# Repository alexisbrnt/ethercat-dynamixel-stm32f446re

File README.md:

# EtherCAT Communication for Dynamixel by STM32F446RE

> An embedded **EtherCAT slave node** built around the STM32F446RE, driving a Dynamixel XM430-W350 servomotor in real time.

---

## About

An embedded EtherCAT slave node based on the **STM32F446RE** microcontroller, designed to drive a **Dynamixel XM430-W350** servomotor through the Dynamixel Protocol 2.0. The STM32 interfaces with an EtherCAT master over SPI (via a LAN9252 slave controller) and translates incoming commands into UART/RS-485 frames sent to the motor.

This project is developed as part of an internship at **Heemskerk Innovative Technology (HIT)**, Delft, The Netherlands.

---

## Goal

Design and implement a new real-time communication architecture allowing an EtherCAT master to command a Dynamixel servomotor (position, velocity, etc.) and read back its live telemetry (position, velocity, current, temperature) with deterministic timing.

**Data path:**

```
EtherCAT Master  ──►  LAN9252 (SPI slave)  ──►  STM32F446RE  ──►  MAX485  ──►  Dynamixel XM430-W350
```

---

## Hardware

| Component | Reference |
|---|---|
| Microcontroller | STM32F446RE (ARM Cortex-M4 @ 180 MHz, 512 KB Flash, 128 KB SRAM) |
| Development board | Nucleo-F446RE (integrated ST-LINK) |
| EtherCAT slave controller | **EVB-LAN9252-SPI** (Microchip evaluation board) |
| Motor | Dynamixel XM430-W350 (Protocol 2.0) |
| UART ↔ RS-485 transceiver | MAX485 |
| Motor power supply | SMPS2Dynamixel |

---

## STM32F446RE Pinout

### Dynamixel communication (UART + RS-485)

| STM32 Pin | Function | Connected to |
|---|---|---|
| **PA9** | UART TX | MAX485 DI |
| **PA10** | UART RX | MAX485 RO |
| **PB3** | DE/RE (RS-485 direction control) | MAX485 DE + RE |

### EtherCAT communication (SPI to LAN9252)

| STM32 Pin | Function | Connected to |
|---|---|---|
| **PA5** | SPI SCK | LAN9252 SCK |
| **PA6** | SPI MISO | LAN9252 MISO |
| **PA7** | SPI MOSI | LAN9252 MOSI |
| **PB6** | SPI CS | LAN9252 CS |

---

## Configuration

| Parameter | Value |
|---|---|
| UART baudrate (STM32 ↔ Dynamixel) | **3,000,000 bauds** (3 Mbps) |
| Dynamixel protocol | **2.0** |
| Default motor ID | **1** |
| SPI frequency (STM32 ↔ LAN9252) | **11.25 MHz** |
| EtherCAT cycle time | **2 ms** |

---

## Usage

### 1. Flash the LAN9252 EEPROM (one-time setup)

Before the EtherCAT master can discover the slave with the correct identity (vendor ID, product code, PDO mapping, etc.), the LAN9252 EEPROM must be programmed with the project's ESI (EtherCAT Slave Information) binary.

The EEPROM image is provided in the firmware sources:

```
STM32_dynamixel/Src/ECAT/soes-esi/eeprom.hex
```

Flash it with the `eepromtool` utility provided by [SOEM](https://github.com/OpenEtherCATsociety/SOEM):

```bash
sudo ./eepromtool <your_network_interface> 1 -wi eeprom.hex
```

- The first argument `1` is the EtherCAT slave position on the bus.
- Replace `<your_network_interface>` (e.g. `eth0`) with the interface connected to the LAN9252.

This step is only required **once per LAN9252 board**, or whenever the ESI / PDO mapping is changed.

### 2. Build and flash the STM32 firmware

1. Open **STM32CubeIDE** 
2. `File → Open Projects from File System…` and select the `firmware/` folder.
3. Build the project: `Project → Build Project` (or `Ctrl+B`).
4. Connect the Nucleo-F446RE over USB and flash: `Run → Run` (or `F11` for debug mode).

### 3. Run the EtherCAT master and GUI

The `ec_motor.py` script is a single-program tool that launches the **EtherCAT master** (using `pysoem`) and a **PyQt5 graphical interface** in the same process. The master runs its cyclic loop (2 ms period) in a dedicated thread and communicates with the GUI through Qt signals.

The GUI allows the user to:

- select the motor **ID** and **control mode** (Position or Velocity),
- set a **target position** (0–4095) or **target velocity** (−200 to +200) through sliders,
- toggle the **torque** and the **LED** on the motor,
- monitor in real time the **present position, velocity, current, temperature**, the motor **state** (`IDLE`, `INIT`, `READY`, `RUNNING`, `ERROR`, `OFF`), the current **operating mode** and the **baudrate**.

**Dependencies** (tested on Linux, Ubuntu/Debian):

```bash
pip install -r scripts/requirements.txt
```

**Launch** (from the root of the repository):

```bash
sudo python3 scripts/ec_motor.py --ifname <your_network_interface>
```

#### Network interface — must be adapted to your machine

The EtherCAT master binds to a specific network interface (the one physically connected to the EtherCAT slave, typically a USB-to-Ethernet adapter). The interface name depends on your hardware and operating system, so **it must be changed in two places**:

1. In the **launch command**, via the `--ifname` argument.
2. In the **default value** inside `scripts/ec_motor.py` (the current hardcoded default is the interface used during development and will not match your setup).

To find the name of your own interface on Linux:

```bash
ip link show
```

Look for an entry matching the adapter you plugged in (often starting with `enx...` for USB-to-Ethernet, or `eth...` / `enp...` for built-in Ethernet).

**Other notes:**

- `sudo` is required because the EtherCAT master sends raw Ethernet frames directly on the network interface.

---

## Resources & references

- [Dynamixel XM430-W350 e-Manual](https://emanual.robotis.com/docs/en/dxl/x/xm430-w350/)
- [Dynamixel Protocol 2.0](https://emanual.robotis.com/docs/en/dxl/protocol2/)
- [STM32F446RE datasheet](https://www.st.com/en/microcontrollers-microprocessors/stm32f446re.html)
- [Microchip LAN9252 product page](https://www.microchip.com/en-us/product/lan9252)
- [EtherCAT Technology Group (ETG)](https://www.ethercat.org/)

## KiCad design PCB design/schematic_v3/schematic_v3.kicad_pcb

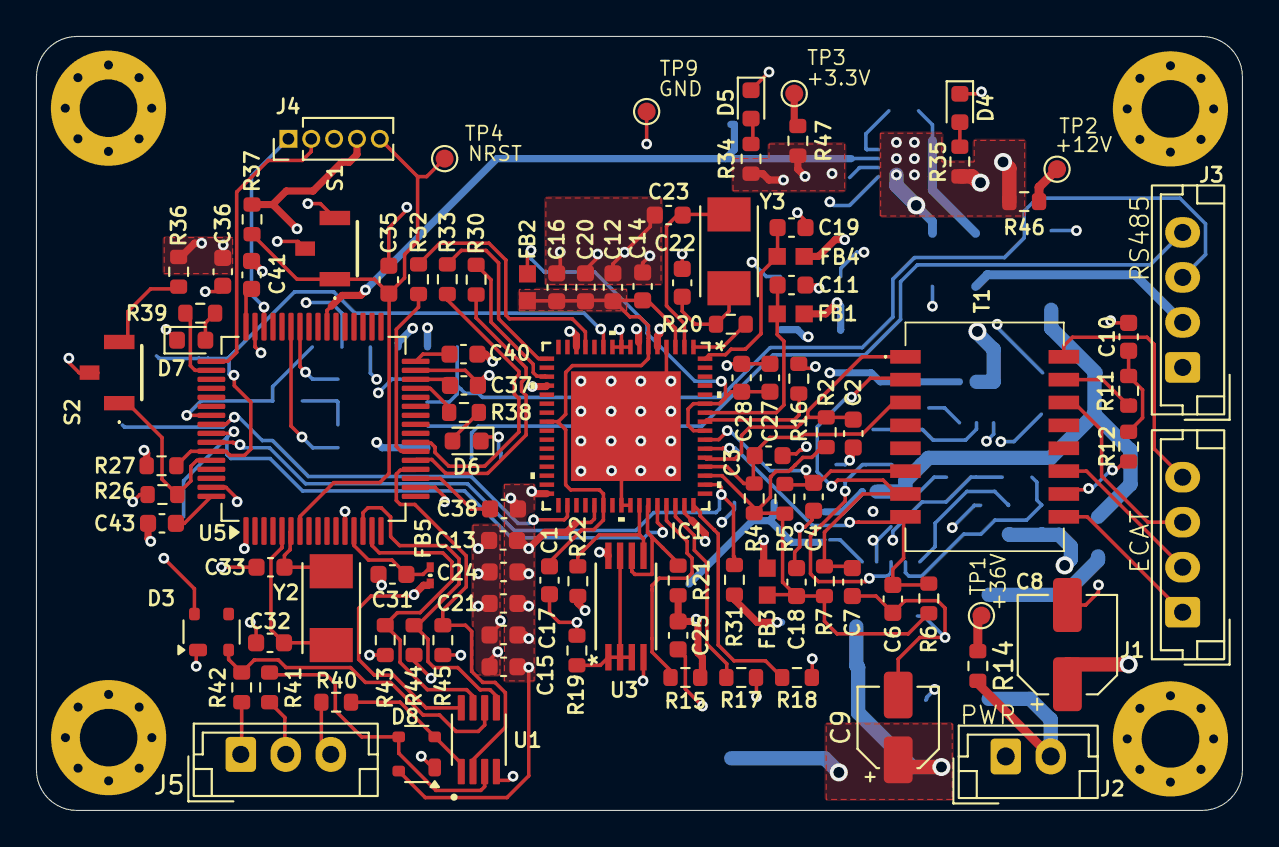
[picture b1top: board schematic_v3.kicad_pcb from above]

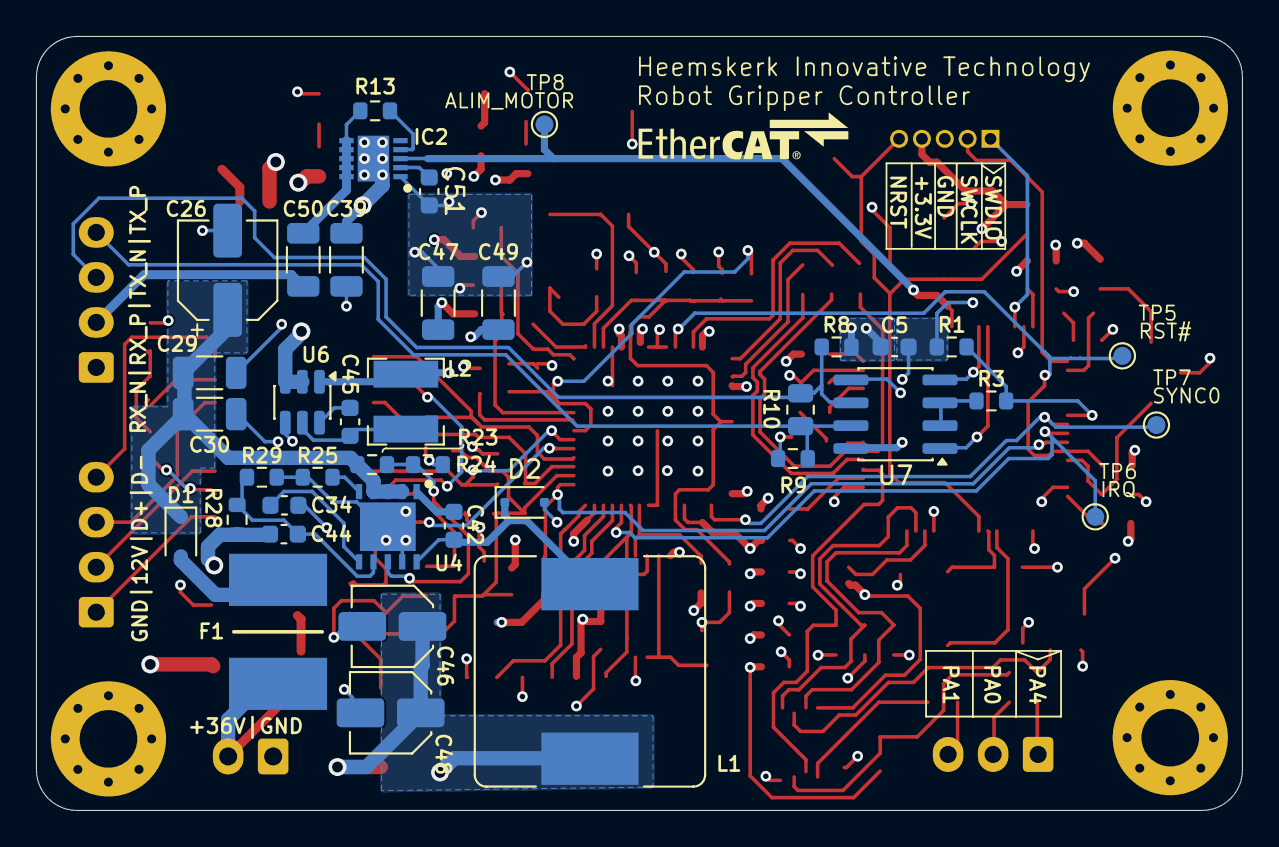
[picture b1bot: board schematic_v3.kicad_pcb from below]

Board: 4 copper layers, 67.0 x 43.0 mm, 145 parts (39 on the bottom side), 93 nets.

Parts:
C1, C5, C11, C13, C15, C16, C17, C20, C21, C24, C25, C27, C28, C31, C34, C35, C38, C40, C41, C42, C43, C45: 100n; C_0603_1608Metric
C2, C3, C4, C6: 10p; C_0603_1608Metric
C7: 0.022u; C_0603_1608Metric
C8: 10u; CP_Elec_5x5.4
C9: 1u; CP_Elec_4x5.4
C10: 1n; C_0603_1608Metric
C12, C18, C19, C36: 1u; C_0603_1608Metric
C14: 470p; C_0603_1608Metric
C22, C23: 18p; C_0603_1608Metric
C26: 47u; CP_Elec_5x5.4
C29, C39, C50: 10u; C_1206_3216Metric
C30: 100n; C_1206_3216Metric
C32, C33: 27p; C_0603_1608Metric
C37: 4.7u; C_0603_1608Metric
C44: 270p; C_0603_1608Metric
C46, C48: 27u; C_Elec_4x5.8
C47, C49: 22u; C_1206_3216Metric
C51: 56p; C_0603_1608Metric
D1, D2: PMEG3020EJ; D_SOD-323F
D3, D8: PRTR5V0U2X; SOT-143
D4, D5, D6, D7: LED_Small; LED_0603_1608Metric
F1: 2920L150_60MR
FB1, FB2, FB3, FB4: BLM18EG221SN1D; IND_BLM18_0603_MUR
FB5: MMZ0603A471ET000
H1, H2, H3, H4: MountingHole; MountingHole_3.2mm_M3_Pad_Via
IC1: LAN9252
IC2: SON50P300X300X100-11N-D; MP5000ADQ-LF-Z
J1: Conn_01x04_Pin; JST_EH_B4B-EH-A_1x04_P2.50mm_Vertical
J2: Conn_01x02_Pin; JST_EH_B2B-EH-A_1x02_P2.50mm_Vertical
J3: connection_moteur; JST_EH_B4B-EH-A_1x04_P2.50mm_Vertical
J4: Conn_01x05_Pin; PinHeader_1x05_P1.27mm_Vertical
J5: Conn_01x03_Pin; JST_EH_B3B-EH-A_1x03_P2.50mm_Vertical
L1: 18u; L_Bourns_SRR1260
L2: 6.8u; L_Bourns-SRN4018
R1: 47k; R_0603_1608Metric
R2, R4, R5, R6: 49.9; R_0603_1608Metric
R3, R15, R17, R18, R24, R26, R27, R29, R31, R37, R43, R44, R45: 10k; R_0603_1608Metric
R7, R20: 0; R_0603_1608Metric
R8, R9, R25: 20k; R_0603_1608Metric
R10: 120; R_0805_2012Metric
R11, R12: 75; R_0603_1608Metric
R13: 220; R_0603_1608Metric
R14, R46, R47: 100; R_0603_1608Metric
R16: 12.1k; R_0603_1608Metric
R19: 4.7k; R_0603_1608Metric
R21, R22, R34, R36, R38, R39, R40, R41, R42: 1k; R_0603_1608Metric
R23: 68k; R_0603_1608Metric
R28: 150k; R_0603_1608Metric
R30, R32, R33: 33; R_0603_1608Metric
R35: 3.3k; R_0603_1608Metric
S1, S2: B3U-1100PM; B3U1100PM
T1: 7490100110A
TP1, TP2, TP3, TP4, TP5, TP6, TP7, TP8, TP9: TestPoint; TestPoint_Pad_D1.0mm
U1: SN74LVC3G17DCTRE4
U3: 24FC512-I/ST; 24FC512_I_ST
U4: LMR14030SQDPRTQ1
U5: STM32F446RETx; LQFP-64_10x10mm_P0.5mm
U6: AP63203WU; TSOT-23-6
U7: MAX3485; SOIC-8_3.9x4.9mm_P1.27mm
Y2: ABM3-20.000MHZ-D2Y-T
Y3: ABM3-25.000MHZ-D2Y-T

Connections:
+3.3V: C5.1, C13.1, C15.1, C17.1, C21.1, C24.1, C25.2, C36.2, C38.1, C40.1, C41.1, C43.1, C47.1, C49.1, D3.4 (VCC), D8.4 (VCC), FB1.1, FB3.2, FB4.2, FB5.1, IC1.5 (VDD33), IC1.7 (REG_EN), IC1.14 (VDDIO0), IC1.20 (VDDIO1), IC1.32 (VDDIO2), IC1.37 (VDDIO3), IC1.47 (VDDIO4), J4.4, L2.2, R8.2, R15.1, R21.2, R22.2, R27.1, R31.1, R34.1, R36.1, R37.2, R47.2, U1.8 (VCC), U3.8 (VCC), U5.1 (VBAT), U6.1 (FB), U7.8 (VCC)
+12V: C8.1, C9.1, C39.1, C44.1, C46.1, C48.1, IC2.11 (VCC), L1.2, R28.1, R35.1, R46.2, U6.2 (EN), U6.3 (IN)
+36V: F1.1, J2.2, R14.2
/ALIM_MOTOR: IC2.3 (ENABLE/FAULT), TP8.1 (1_1), U5.39 (PC8)
/AVDD: C31.1, FB5.2, U5.13 (VDDA)
/AX: R19.1, U3.1 (A0), U3.2 (A1), U3.3 (A2), U3.7 (WP)
/BOOT: C42.1, U4.1 (BOOT)
/BOOT0: R26.1, S2.1 (COM), U5.60 (BOOT0)
/BST: C45.2, U6.6 (BST)
/CMT: C10.1, R11.1, R12.1
/CMT1: R11.2, T1.15 (CTX)
/CMT2: R12.2, T1.10 (CRX)
/DATA+: J3.3, R8.1, R10.2, U7.6 (A)
/DATA-: J3.4, R9.2, R10.1, U7.7 (B)
/DE/RE: R3.1, U7.2 (~RE), U7.3 (DE)
/DI: U5.42 (PA9), U7.4 (DI)
/FB: C44.2, R28.2, R29.1, U4.7 (FB)
/I2C_SCL: IC1.43 (EESCL/TCK), R21.1, U3.6 (SCL)
/I2C_SDL: IC1.42 (EESDA/TMS), R22.1, U3.5 (SDA)
/IRQ: IC1.44 (IRQ), TP6.1 (1_1), U5.57 (PB5)
/MISO: IC1.13 (D1/AD1/EOF/SO/SIO1), R32.1
/MOSI: IC1.17 (D0/AD0/WD_STATE/SI/SIO0), R33.1
/NRST: C35.2, J4.5, R37.1, S1.1 (COM), TP4.1 (1_1), U5.7 (NRST)
/OSCI: IC1.1 (OSCI), R20.1
/OSCO: C23.2, IC1.2 (OSCO), Y3.1
/PA0: R44.1, U1.5 (2Y), U5.14 (PA0)
/PA1: R43.1, U1.7 (1Y), U5.15 (PA1)
/PA4: R45.1, U1.2 (3Y), U5.20 (PA4)
/PA5: R30.2, U5.21 (PA5)
/PA6: R32.2, U5.22 (PA6)
/PA7: R33.2, U5.23 (PA7)
/PA15: R39.1, U5.50 (PA15)
/PB10: R38.1, U5.29 (PB10)
/PGOOD: R23.2, R24.1, U4.8 (PGOOD)
/PH0: C32.2, U5.5 (PH0), Y2.2
/PH1: C33.2, U5.6 (PH1), Y2.1
/RBIAS: IC1.57 (RBIAS), R16.2
/RCT: C7.1, R7.2, T1.2 (CTD), T1.7 (CRD)
/RO: U5.43 (PA10), U7.1 (RO)
/RS485_MODE: R1.2, R3.2, U5.55 (PB3)
/RST#: IC1.11 (RST#), R27.2, TP5.1 (1_1), U5.59 (PB7)
/RT_SYNC: R25.1, U4.5 (RT_SYNC)
/RXA_N: C6.1, IC1.54 (RXNA), R6.2, T1.8 (RD-)
/RXA_P: C4.1, IC1.55 (RXPA), R5.2, T1.6 (RD+)
/RX_N: J1.1, T1.9 (RX-)
/RX_P: J1.2, T1.11 (RX+)
/SCK: IC1.19 (D9/AD9/LATCH_IN/SCK), R30.1
/SCS#: IC1.50 (D5/AD5/OUTVALID/SCS#), R31.2, U5.58 (PB6)
/SS: C34.1, U4.6 (SS)
/SW: C45.1, L2.1, U6.5 (SW)
/SWCLK: J4.2, U5.49 (PA14)
/SWDIO: J4.1, U5.46 (PA13)
/SYNC0: IC1.34 (SYNC0/LATCH0), TP7.1 (1_1), U5.56 (PB4)
/TXA_N: C3.1, IC1.52 (TXNA), R4.2, T1.3 (TD-)
/TXA_P: C2.1, IC1.53 (TXPA), R2.2, T1.1 (TD+)
/TX_N: J1.3, T1.14 (TX-)
/TX_P: J1.4, T1.16 (TX+)
/VCAP_1: C37.1, U5.30 (VCAP_1)
/VDD12TX1: C27.1, C28.1, FB2.2, IC1.56 (VDD12TX1), IC1.59 (VDD12TX2)
/VDD19: C38.2, U5.19 (VDD)
/VDD32: C40.2, U5.32 (VDD)
/VDD33BIAS: C11.2, FB1.2, IC1.58 (VDD33BIAS)
/VDD33TXRX1: C18.1, FB3.1, IC1.51 (VDD33TXRX1), R2.1, R4.1, R5.1, R6.1, R7.1
/VDD33TXRX2: C19.1, FB4.1, IC1.64 (VDD33TXRX2)
/VDD48: C41.2, U5.48 (VDD)
/VDD64: C43.2, U5.64 (VDD)
/VDDCR: C1.2, C12.1, C14.1, C16.1, C20.1, FB2.1, IC1.3 (OSCVDD12), IC1.6 (VDDCR0), IC1.24 (VDDCR1), IC1.38 (VDDCR2)
/VIN: C26.1, C29.1, C30.1, D1.1 (K), R23.1, U4.2 (VIN), U4.3 (VIN), U4.4 (EN)
GND: C1.1, C2.2, C3.2, C4.2, C5.2, C6.2, C7.2, C8.2, C9.2, C11.1, C12.2, C13.2, C14.2, C15.2, C16.2, C17.2, C18.2, C19.2, C20.2, C21.2, C22.1, C23.1, C24.2, C25.1, C26.2, C27.2, C28.2, C29.2, C30.2, C31.2, C32.1, C33.1, C34.2, C35.1, C36.1, C37.2, C39.2, C46.2, C47.2, C48.2, C49.2, C51.1, D2.2 (A), D3.1 (GND), D4.1 (K), D5.1 (K), D6.1 (K), D7.1 (K), D8.1 (GND), IC1.4 (OSCVSS), IC1.8 (FXLOSEN), IC1.9 (FXSDA/FXLOSA/FXSDENA), IC1.10 (FXSDB/FXLOSB/FXSDENB), IC1.40 (D8/AD8/DIGIO2/GPI2/GPO2/MII_MDIO), IC1.41 (TESTMODE), IC1.65 (VSS), IC2.1 (GND), J2.1, J3.1, J4.3, R1.1, R9.1, R16.1, R17.1, R18.1, R19.2, R24.2, R25.2, R26.2, R29.2, R43.2, R44.2, R45.2, S1.2 (NO), S1.3 (GND), S2.3 (GND), TP9.1 (1_1), U1.4 (GND), U3.4 (VSS), U4.9 (GND), U4.11 (PAD), U5.12 (VSSA), U5.18 (VSS), U5.31 (VSS), U5.47 (VSS), U5.63 (VSS), U6.4 (GND), U7.5 (GND)
unnamed: C22.2, R20.2, Y3.2
unnamed: D1.2 (A), F1.2
unnamed: C42.2, D2.1 (K), L1.1, U4.10 (SW)
unnamed: D3.2 (I/O1), R42.1, U1.6 (3A)
unnamed: D4.2 (A), R35.2
unnamed: D5.2 (A), R34.2
unnamed: D6.2 (A), R38.2
unnamed: D7.2 (A), R39.2
unnamed: D8.2 (I/O1), R40.1, U1.1 (1A)
unnamed: D8.3 (I/O2), R41.1, U1.3 (2A)
unnamed: IC1.48 (LINKACTLED0/TDO/CHIP_MODE0), R18.2
unnamed: IC1.46 (LINKACTLED1/TDI/CHIP_MODE1), R17.2
unnamed: IC1.45 (RUNLED/E2PSIZE), R15.2
unnamed: C51.2, IC2.2 (DV/DT)
unnamed: IC2.4 (I-LIMIT), R13.1
unnamed: C50.1, IC2.6 (SOURCE_1), IC2.7 (SOURCE_2), IC2.8 (SOURCE_3), IC2.9 (SOURCE_4), IC2.10 (SOURCE_5), R13.2
unnamed: C50.2, J3.2
unnamed: J5.1, R42.2
unnamed: J5.2, R41.2
unnamed: J5.3, R40.2
unnamed: R14.1, TP1.1 (1_1)
unnamed: R46.1, TP2.1 (1_1)
unnamed: R47.1, TP3.1 (1_1)
unnamed: R36.2, S2.2 (NO)

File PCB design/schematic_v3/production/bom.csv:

Designator,Footprint,Quantity,Value,LCSC Part #
"C1, C11, C13, C15, C16, C17, C20, C21, C24, C25, C27, C28, C31, C34, C35, C38, C40, C41, C42, C43, C45, C5",603,22,100n,C1525
C10,603,1,1n,C1588
"C12, C18, C19, C36",603,4,1u,C15849
C14,603,1,470p,C1620
"C2, C3, C4, C6",603,4,10p,C1634
"C22, C23",603,2,18p,C1647
C26,CP_Elec_5x5.4,1,47u,C7469972
"C29, C39, C50",1206,3,10u,C13585
C30,1206,1,100n,C24497
"C32, C33",603,2,27p,C107045
C37,603,1,4.7u,C19666
C44,603,1,270p,C1608
"C46, C48",C_Elec_4x5.8,2,27u,C413624
"C47, C49",1206,2,22u,C12891
C51,603,1,56p,C107053
C7,603,1,0.022u,C21122
C8,CP_Elec_5x5.4,1,10u,C7469956
C9,CP_Elec_4x5.4,1,1u,C3348
"D1, D2",D_SOD-323F,2,PMEG3020EJ,C7472895
"D3, D8",SOT-143,2,PRTR5V0U2X,C2827688
D4,603,1,LED_Small,C2286
D5,603,1,LED_Small,C2287
D6,603,1,LED_Small,C2288
D7,603,1,LED_Small,C2289
F1,2920L150_60MR,1,2920L150_60MR,C22504886
"FB1, FB2, FB3, FB4",IND_BLM18_0603_MUR,4,BLM18EG221SN1D,C85827
FB5,MMZ0603A471ET000,1,MMZ0603A471ET000,C502003
IC1,LAN9252,1,LAN9252,C2758355
IC2,MP5000ADQ-LF-Z,1,MP5000ADQ-LF-Z,C17698177
J1,JST_EH_B4B-EH-A_1x04_P2.50mm_Vertical,1,Conn_01x04_Pin,C160258
J2,JST_EH_B2B-EH-A_1x02_P2.50mm_Vertical,1,Conn_01x02_Pin,C160262
J3,JST_EH_B4B-EH-A_1x04_P2.50mm_Vertical,1,connection_moteur,C160258
J4,PinHeader_1x05_P1.27mm_Vertical,1,Conn_01x05_Pin,C22438102
J5,JST_EH_B3B-EH-A_1x03_P2.50mm_Vertical,1,Conn_01x03_Pin,C160259
L1,L_Bourns_SRR1260,1,18u,C2042399
L2,L_Bourns-SRN4018,1,6.8u,C2044369
R1,603,1,47k,C25819
R10,805,1,120,C17437
"R11, R12",603,2,75,C4275
R13,603,1,220,C22962
"R14, R46, R47",603,3,100,C22775
"R15, R17, R18, R24, R26, R27, R29, R3, R31, R37, R43, R44, R45",603,13,10k,C309083
R16,603,1,12.1k,C22864
R19,603,1,4.7k,C23162
"R2, R4, R5, R6",603,4,49.9,C23185
"R20, R7",603,2,0,C21189
"R21, R22, R34, R36, R38, R39, R40, R41, R42",603,9,1k,C21190
R23,603,1,68k,C23231
"R25, R8, R9",603,3,20k,C4184
R28,603,1,150k,C22807
"R30, R32, R33",603,3,33,C23140
R35,603,1,3.3k,C22978
"S1, S2",B3U1100PM,2,B3U-1100PM,C6467298
T1,7490100110A,1,7490100110A,C55061081
"TP1, TP2, TP3, TP4, TP5, TP6, TP7, TP8, TP9",TestPoint_Pad_D1.0mm,9,TestPoint,
U1,SN74LVC3G17DCTRE4,1,SN74LVC3G17DCTRE4,C19948350
U3,24FC512_I_ST,1,24FC512-I/ST,C619635
U4,LMR14030SQDPRTQ1,1,LMR14030SQDPRTQ1,C425925
U5,LQFP-64_10x10mm_P0.5mm,1,STM32F446RETx,C69336
U6,TSOT-23-6,1,AP63203WU,C780769
U7,SOIC-8_3.9x4.9mm_P1.27mm,1,MAX3485,C9943
Y2,ABM3-20.000MHZ-D2Y-T,1,ABM3-20.000MHZ-D2Y-T,C596863
Y3,ABM3-25.000MHZ-D2Y-T,1,ABM3-25.000MHZ-D2Y-T,C148312

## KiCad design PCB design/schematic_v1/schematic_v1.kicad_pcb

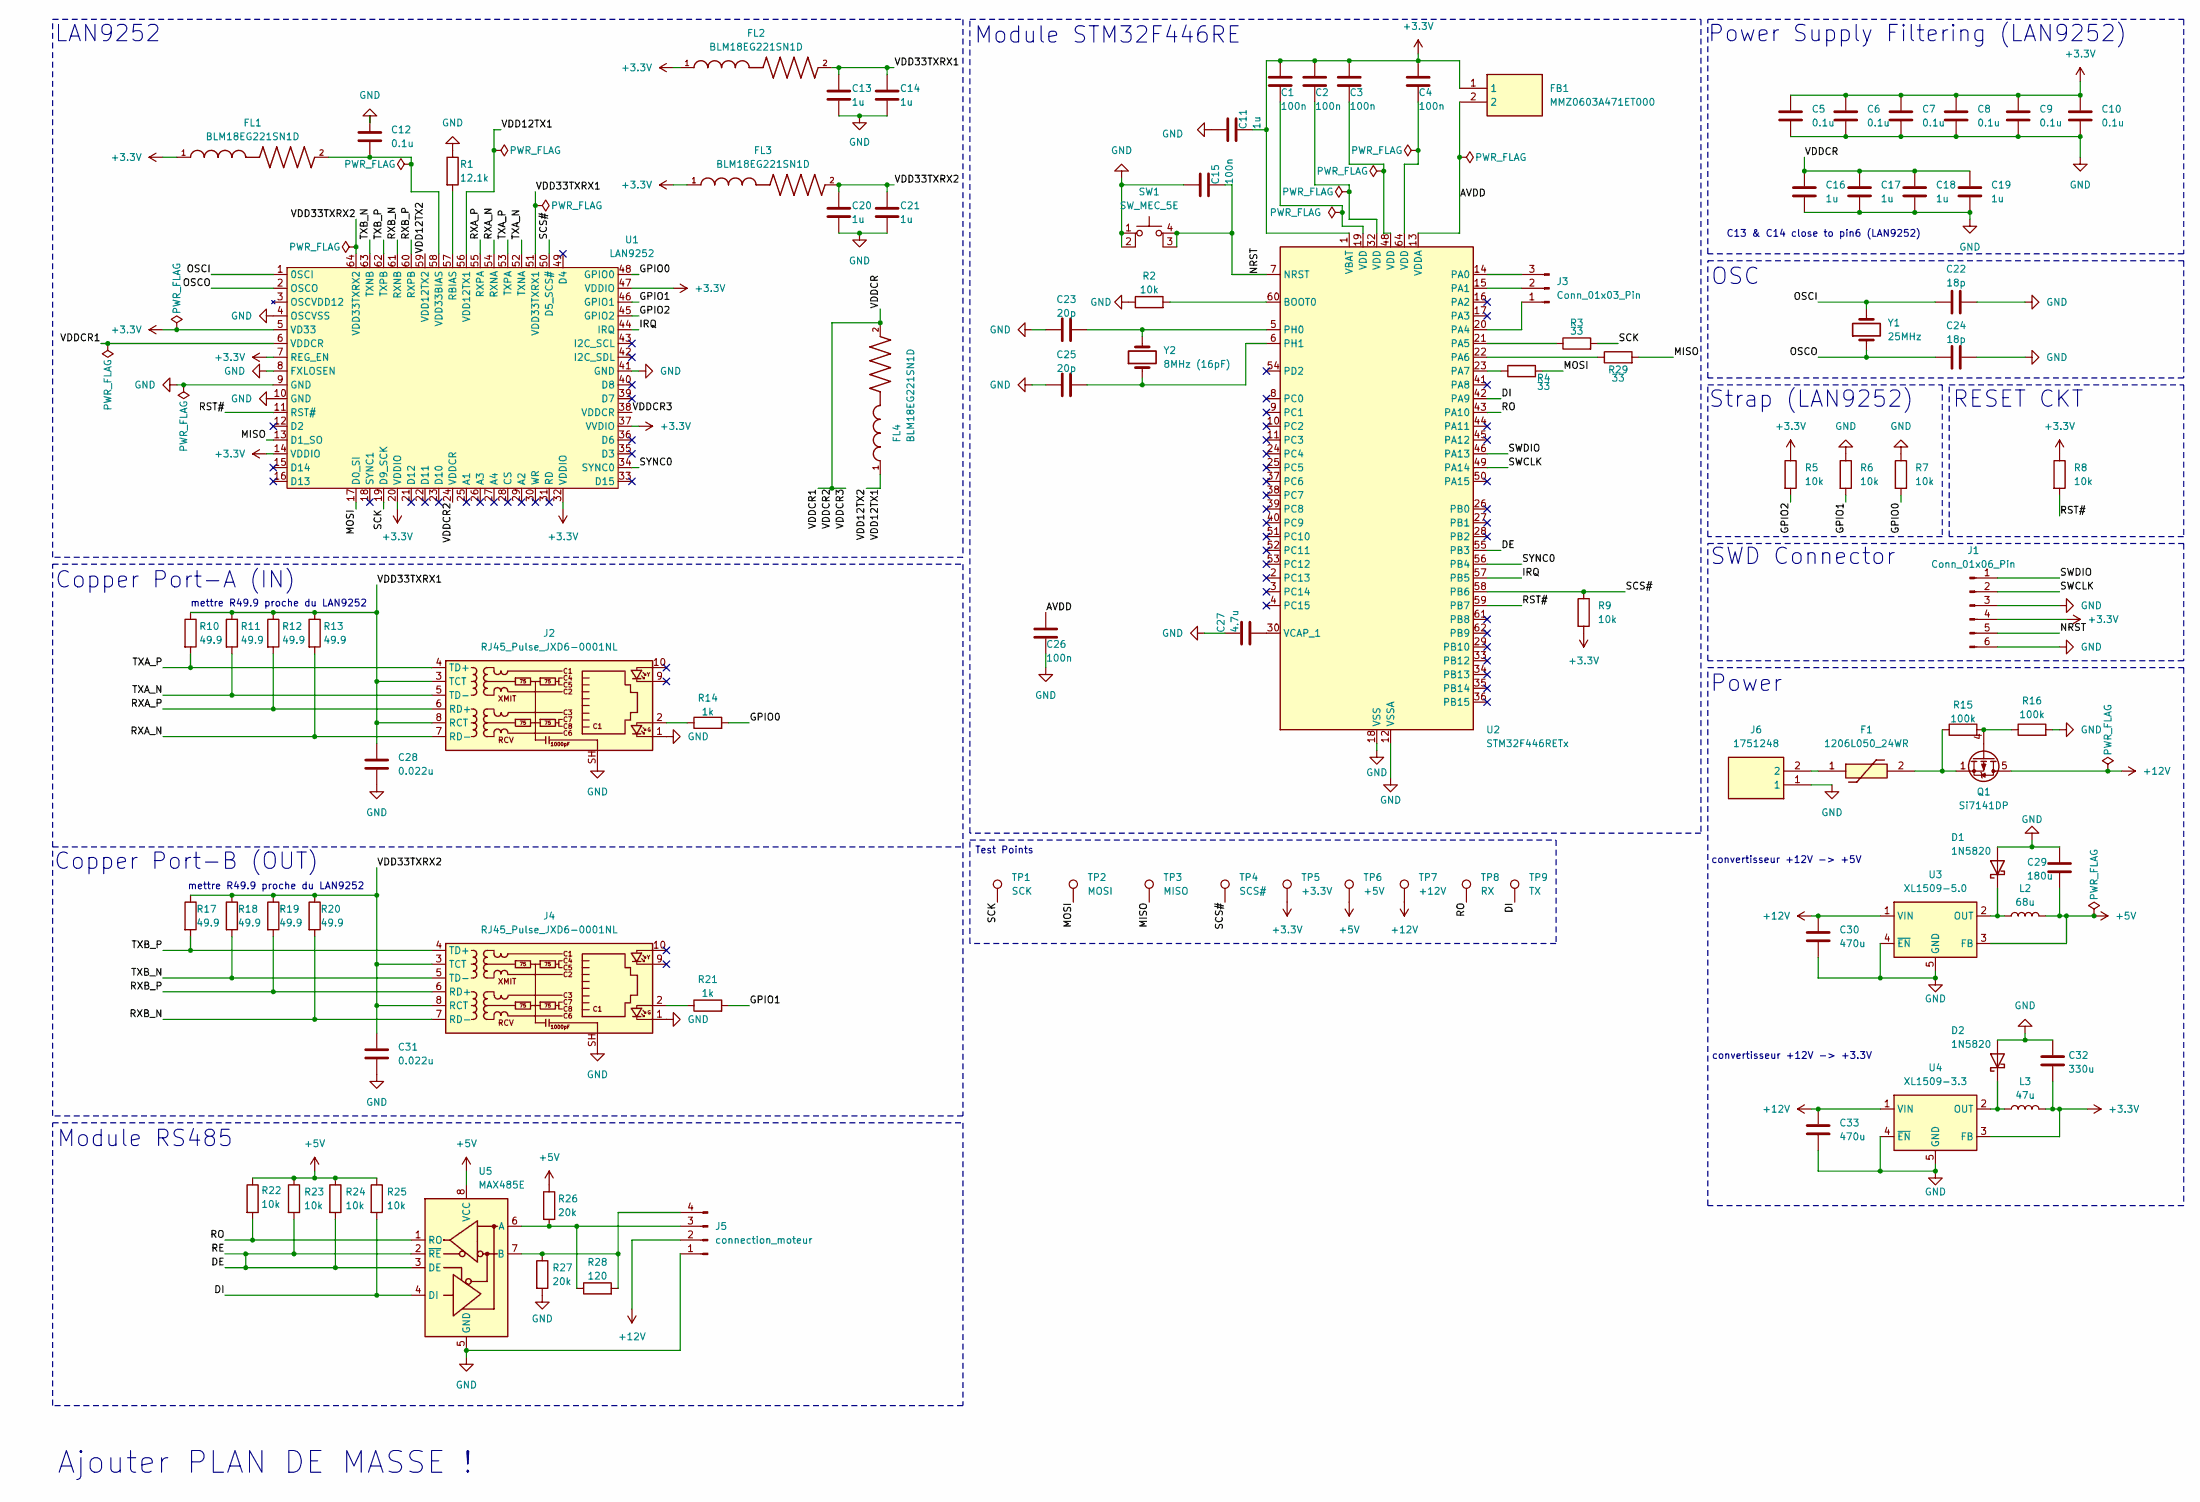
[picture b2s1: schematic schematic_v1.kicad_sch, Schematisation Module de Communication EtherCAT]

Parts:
C1: 100n; BNC_Amphenol_B6252HB-NPP3G-50_Horizontal
C2, C3, C4, C15, C26: 100n; C_0805_2012Metric_Pad1.18x1.45mm_HandSolder
C5, C6, C7, C8, C9, C10, C12: 0.1u; C_0805_2012Metric_Pad1.18x1.45mm_HandSolder
C11, C13, C14, C16, C17, C18, C19, C20, C21: 1u; C_0805_2012Metric_Pad1.18x1.45mm_HandSolder
C22, C24: 18p; C_0805_2012Metric_Pad1.18x1.45mm_HandSolder
C23, C25: 20p; C_0805_2012Metric_Pad1.18x1.45mm_HandSolder
C27: 4.7u; C_Elec_5x5.4
C28, C31: 0.022u; C_0805_2012Metric_Pad1.18x1.45mm_HandSolder
C29: 180u; C_0805_2012Metric_Pad1.18x1.45mm_HandSolder
C30: 470u; C_Elec_5x5.4
C32: 330u; C_Elec_5x5.4
C33: 470u; C_0805_2012Metric_Pad1.18x1.45mm_HandSolder
D1, D2: 1N5820; D_DO-201AD_P15.24mm_Horizontal
F1: 1206L050_24WR; 1206L075132WR; Mouser Part Number 576-1206L050/24WR
FB1: MMZ0603A471ET000; BEADC0603X33N; Mouser Part Number 810-MMZ0603A471ET000
FL1, FL2, FL3, FL4: BLM18EG221SN1D; BEADC1608X95N
J1: Conn_01x06_Pin; PinHeader_2x03_P1.27mm_Vertical
J2, J4: RJ45_Pulse_JXD6-0001NL; RJ45_Pulse_JXD6-0001NL_Horizontal
J3: Conn_01x03_Pin; PinHeader_1x03_P1.27mm_Vertical
J5: connection_moteur; JST_EH_B4B-EH-A_1x04_P2.50mm_Vertical
J6: 1751248; Mouser Part Number 651-1751248
L2: 68u; L_Wurth_WE-LQSH-4020
L3: 47u; L_Wurth_WE-LQSH-4020
Q1: Si7141DP; PowerPAK_SO-8_Single
R1: 12.1k; R_0805_2012Metric_Pad1.20x1.40mm_HandSolder
R2, R5, R6, R7, R8, R9, R22, R23, R24, R25: 10k; R_0805_2012Metric_Pad1.20x1.40mm_HandSolder
R3, R4, R29: 33; R_0805_2012Metric_Pad1.20x1.40mm_HandSolder
R10, R11, R12, R13, R17, R18, R19, R20: 49.9; R_0805_2012Metric_Pad1.20x1.40mm_HandSolder
R14, R21: 1k; R_0805_2012Metric_Pad1.20x1.40mm_HandSolder
R15, R16: 100k; R_0805_2012Metric_Pad1.20x1.40mm_HandSolder
R26, R27: 20k; R_0805_2012Metric_Pad1.20x1.40mm_HandSolder
R28: 120; R_0805_2012Metric_Pad1.20x1.40mm_HandSolder
SW1: SW_MEC_5E; SW_MEC_5GSH9
TP1: SCK; TestPoint_Keystone_5015_Micro_Mini
TP2: MOSI; TestPoint_Keystone_5015_Micro_Mini
TP3: MISO; TestPoint_Keystone_5015_Micro_Mini
TP4: SCS#; TestPoint_Keystone_5015_Micro_Mini
TP5: +3.3V; TestPoint_Keystone_5015_Micro_Mini
TP6: +5V; TestPoint_Keystone_5015_Micro_Mini
TP7: +12V; TestPoint_Keystone_5015_Micro_Mini
TP8: RX; TestPoint_Keystone_5015_Micro_Mini
TP9: TX; TestPoint_Keystone_5015_Micro_Mini
U1: LAN9252; QFN-64-1EP_9x9mm_P0.5mm_EP6x6mm
U2: STM32F446RETx; LQFP-64_10x10mm_P0.5mm
U3: XL1509-5.0; SOIC-8_3.9x4.9mm_P1.27mm
U4: XL1509-3.3; SOIC-8_3.9x4.9mm_P1.27mm
U5: MAX485E; SOIC-8_3.9x4.9mm_P1.27mm
Y1: 25MHz; Crystal_SMD_HC49-SD
Y2: 8MHz (16pF); Crystal_SMD_HC49-SD

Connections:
+3.3V: C1.1, C2.1, C3.1, C4.1, C5.1, C6.1, C7.1, C8.1, C9.1, C10.1, C11.2, C32.2, FB1.1, FL1.1, FL2.1, FL3.1, J1.4, L3.2, R5.1, R8.1, R9.2, TP5.1, U1.5 (VD33), U1.7 (REG_EN), U1.14 (VDDIO), U1.20 (VDDIO), U1.32 (VDDIO), U1.37 (VVDIO), U1.47 (VDDIO), U2.1 (VBAT), U4.3 (FB)
+5V: C29.2, L2.2, R22.1, R23.1, R24.1, R25.1, R26.1, TP6.1, U3.3 (FB), U5.8 (VCC)
+12V: C30.1, C33.1, J5.2, Q1.5 (D), TP7.1, U3.1 (VIN), U4.1 (VIN)
/AVDD: C26.1, FB1.2, U2.13 (VDDA)
/DE: R23.2, R24.2, U2.55 (PB3), U5.2 (~RE), U5.3 (DE)
/DI: R25.2, TP9.1, U2.42 (PA9), U5.4 (DI)
/GPIO0: R7.2, R14.2, U1.48 (GPIO0)
/GPIO1: R6.2, R21.2, U1.46 (GPIO1)
/GPIO2: R5.2, U1.45 (GPIO2)
/IRQ: U1.44 (IRQ), U2.57 (PB5)
/MISO: R29.2, TP3.1, U1.13 (D1_SO)
/MOSI: R4.2, TP2.1, U1.17 (D0_SI)
/NRST: C15.2, J1.5, SW1.3 (K), SW1.4 (A), U2.7 (NRST)
/OSCI: C22.2, U1.1 (0SCI), Y1.2
/OSCO: C24.2, U1.2 (OSCO), Y1.1
/RO: R22.2, TP8.1, U2.43 (PA10), U5.1 (RO)
/RST#: R8.2, U1.11 (RST#), U2.59 (PB7)
/RXA_N: J2.7 (RD-), R13.2, U1.54 (RXNA)
/RXA_P: J2.6 (RD+), R12.2, U1.55 (RXPA)
/RXB_N: J4.7 (RD-), R20.2, U1.61 (RXNB)
/RXB_P: J4.6 (RD+), R19.2, U1.60 (RXPB)
/SCK: R3.2, TP1.1, U1.19 (D9_SCK)
/SCS#: R9.1, TP4.1, U1.50 (D5_SCS#), U2.58 (PB6)
/SYNC0: U1.34 (SYNC0), U2.56 (PB4)
/TXA_N: J2.5 (TD-), R11.2, U1.52 (TXNA)
/TXA_P: J2.4 (TD+), R10.2, U1.53 (TXPA)
/TXB_N: J4.5 (TD-), R18.2, U1.63 (TXNB)
/TXB_P: J4.4 (TD+), R17.2, U1.62 (TXPB)
/VDD12TX1: FL4.1, U1.56 (VDD12TX1), U1.59 (VDD12TX2)
/VDD33TXRX1: C13.1, C14.1, C28.1, FL2.2, J2.3 (TCT), J2.8 (RCT), R10.1, R11.1, R12.1, R13.1, U1.51 (VDD33TXRX1)
/VDD33TXRX2: C20.1, C21.1, C31.1, FL3.2, J4.3 (TCT), J4.8 (RCT), R17.1, R18.1, R19.1, R20.1, U1.64 (VDD33TXRX2)
/VDDCR: C16.1, C17.1, C18.1, C19.1, FL4.2, U1.6 (VDDCR), U1.24 (VDDCR), U1.38 (VDDCR)
GND: C5.2, C6.2, C7.2, C8.2, C9.2, C10.2, C11.1, C12.1, C13.2, C14.2, C15.1, C16.2, C17.2, C18.2, C19.2, C20.2, C21.2, C22.1, C23.1, C24.1, C25.1, C26.2, C27.1, C28.2, C29.1, C30.2, C31.2, C32.1, C33.2, D1.2 (A), D2.2 (A), J1.3, J1.6, J2.1, J2.SH, J4.1, J4.SH, J5.1, J6.1, R1.1, R2.1, R6.1, R7.1, R16.2, R27.2, SW1.1, SW1.2, U1.4 (OSCVSS), U1.8 (FXLOSEN), U1.9 (GND), U1.10 (GND), U1.41 (GND), U2.12 (VSSA), U2.18 (VSS), U2.31 (VSS), U2.47 (VSS), U2.63 (VSS), U3.4 (~EN), U3.5 (GND), U3.6 (GND), U3.7 (GND), U3.8 (GND), U4.4 (~EN), U4.5 (GND), U4.6 (GND), U4.7 (GND), U4.8 (GND), U5.5 (GND)
unnamed: C1.2, U2.19 (VDD)
unnamed: C2.2, U2.32 (VDD)
unnamed: C3.2, U2.48 (VDD)
unnamed: C4.2, U2.64 (VDD)
unnamed: D1.1 (K), L2.1, U3.2 (OUT)
unnamed: D2.1 (K), L3.1, U4.2 (OUT)
unnamed: F1.1, J6.2
unnamed: F1.2, Q1.1 (S), Q1.2 (S), Q1.3 (S), R15.1
unnamed: J2.2, R14.1
unnamed: J3.1, U2.20 (PA4)
unnamed: J3.2, U2.15 (PA1)
unnamed: J3.3, U2.14 (PA0)
unnamed: J4.2, R21.1
unnamed: J5.3, R26.2, R28.1, U5.6 (A)
unnamed: J5.4, R27.1, R28.2, U5.7 (B)
unnamed: Q1.4 (G), R15.2, R16.1
unnamed: R1.2, U1.57 (RBIAS)
unnamed: C12.2, FL1.2, U1.58 (VDD33BIAS)
unnamed: R2.2, U2.60 (BOOT0)
unnamed: R3.1, U2.21 (PA5)
unnamed: R29.1, U2.22 (PA6)
unnamed: R4.1, U2.23 (PA7)
unnamed: C23.2, U2.5 (PH0), Y2.2
unnamed: C25.2, U2.6 (PH1), Y2.1
unnamed: C27.2, U2.30 (VCAP_1)

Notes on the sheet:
Ajouter PLAN DE MASSE !
mettre R49.9 proche du LAN9252
Module STM32F446RE
OSC
Copper Port-B (OUT)
C13 & C14 close to pin6 (LAN9252)
Test Points
convertisseur +12V -> +3.3V
Module RS485
Copper Port-A (IN)
Power Supply Filtering (LAN9252)
Strap (LAN9252)
SWD Connector
convertisseur +12V -> +5V
Power
RESET CKT
LAN9252

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
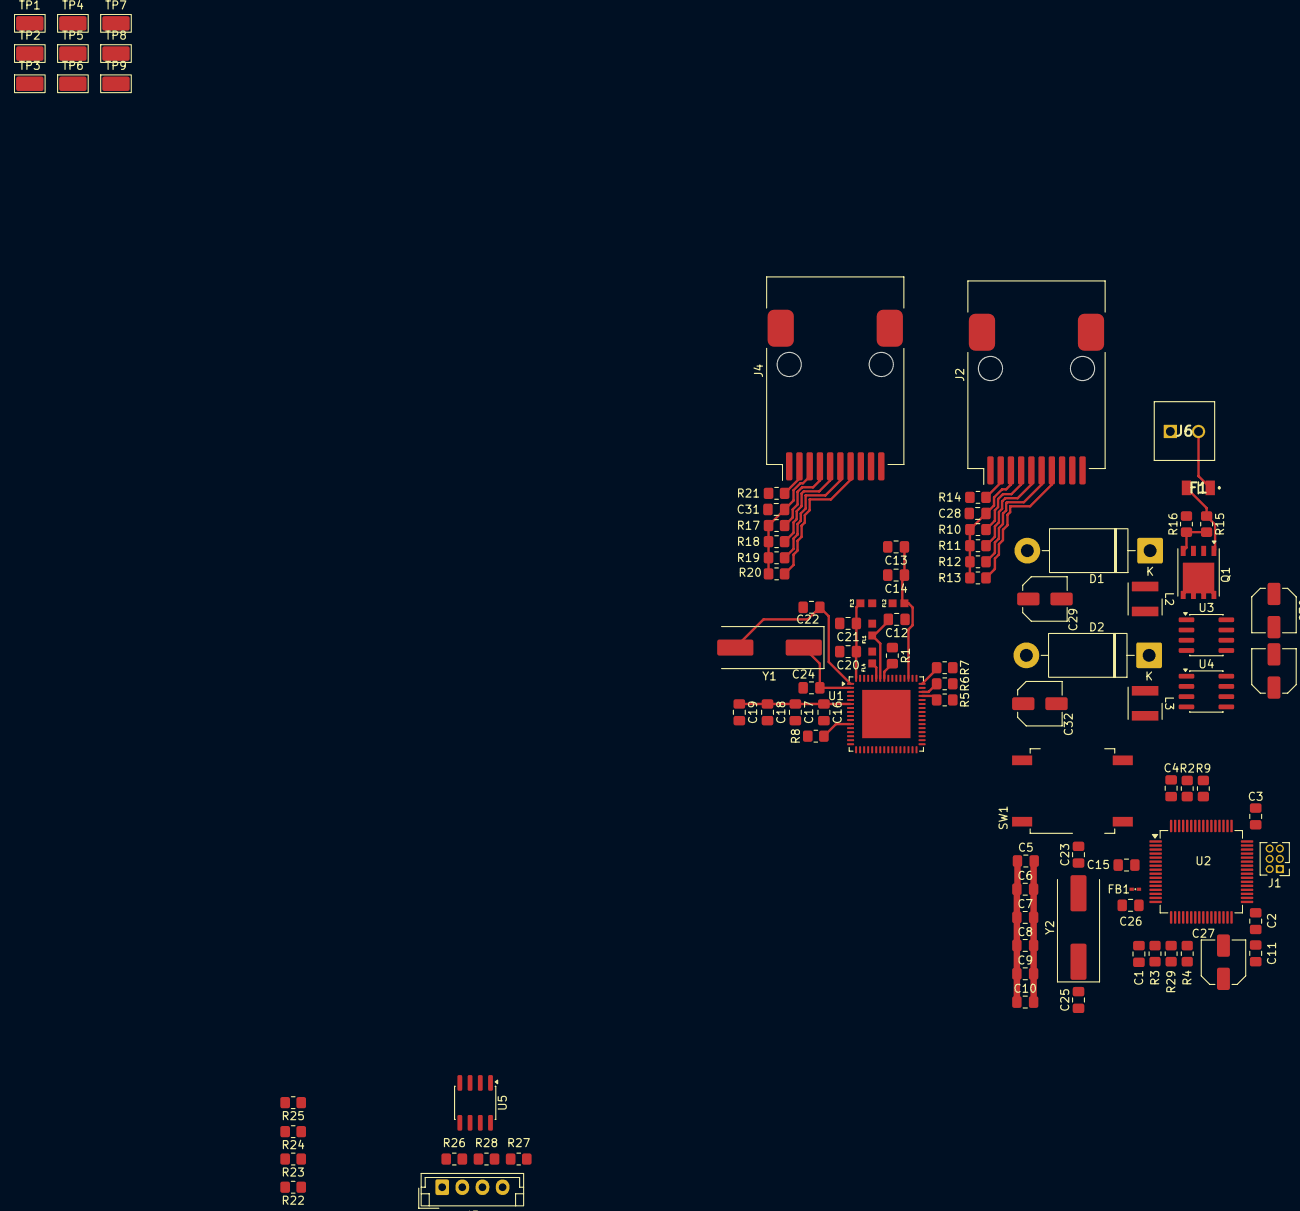
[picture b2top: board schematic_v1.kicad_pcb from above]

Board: 2 copper layers, 95 parts (0 on the bottom side), 57 nets.
